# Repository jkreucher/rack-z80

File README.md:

# Rack Z80 Computer

Copyright 2021 Jannik Kreucher

**NOTE: This Project is still work in progress and not working at this point !**

## Table of Contents
 - [About The Project](#about-the-project)
 - [Folder Structure](#folder-structure)
 - [Modules](#modules)

## About The Project

The goal of this project is to understand how computers and operating systems work. This is a collection of hardware and software to create a multi purpose 8-Bit computer with the popular [ZiLog Z80](https://de.wikipedia.org/wiki/Zilog_Z80) processor as the heart of this project. Everything is contained in a [Eurocard Subrack](https://en.wikipedia.org/wiki/Eurocard_(printed_circuit_board)) formfactor because I really like the industrial look to it. This makes it really flexible and easy to expand (and good looking of course). All the parts used should still be manufacured and every PCB is etched at home so everyone can reproduce this project. I know chinese PCB houses are fairly cheap these days but I love tinkering and I have the PCB right away and dont need to wait 2 weeks for the next revision because it seems like the first design is never working.

## Folder Structure

The project is divided into following directories:
 - code
 - schematics
 - tools

[`schematics/`](schematics) contains all the PCBs I designed for this project. Each board has its own README file for way more detailed information. [`code/`](code) contains the source code for the Z80 computer itself. The directory [`tools/`](tools) contains everything needed to compile, assemble source code and other software for this project.

## Modules
To get more information about one module click on the link.
 - [Processor Board](schematics/RackZ80_Processor)
 - [RS232 Serial Interface](schematics/RackZ80_RS232)

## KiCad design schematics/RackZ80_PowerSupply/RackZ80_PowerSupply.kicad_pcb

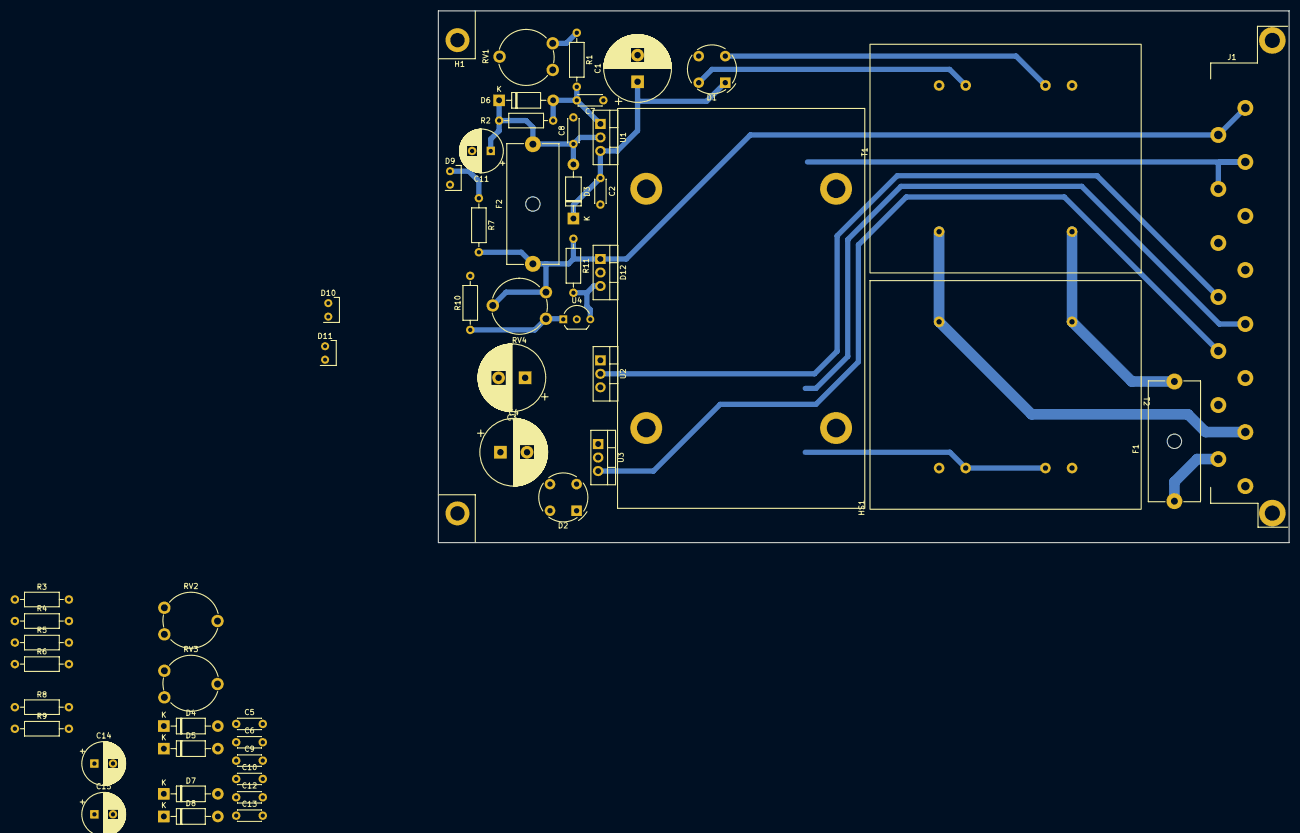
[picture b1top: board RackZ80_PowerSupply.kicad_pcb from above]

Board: 2 copper layers, 160.0 x 100.0 mm, 53 parts (0 on the bottom side), 27 nets.

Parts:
C1, C3, C4: 2200u; CP_Radial_D12.5mm_P5.00mm
C2, C5, C6, C7, C8, C9, C10, C12, C13: 100n; C_Disc_D4.3mm_W1.9mm_P5.00mm
C11, C14, C15: 470u; CP_Radial_D8.0mm_P3.50mm
D1, D2: D_Bridge_+A-A; Diode_Bridge_Round_D9.0mm
D3, D4, D5, D6, D7, D8: 1N4002; D_DO-41_SOD81_P10.16mm_Horizontal
D9, D10, D11: LED; LED_Kingbright_T-1_3mm
D12: BT138; TO-220-3_Vertical
F1: 100mA Slow; Fuseholder_Cylinder-5x20mm_Schurter_0031_8201_Horizontal_Op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
F2: 1A Fast; Fuseholder_Cylinder-5x20mm_Schurter_0031_8201_Horizontal_Op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
H1: FrontPanel; Eurocard_FrontPanel
HS1: Heatsink; Heatsink_Fischer_SK68_75mm
J1: DIN41612 H15; DIN41612_H_right_angle
R1, R8, R9: 1k; R_Axial_DIN0207_L6.3mm_D2.5mm_P10.16mm_Horizontal
R2, R10: 470R; R_Axial_DIN0207_L6.3mm_D2.5mm_P10.16mm_Horizontal
R3, R4: 1k8; R_Axial_DIN0207_L6.3mm_D2.5mm_P10.16mm_Horizontal
R5, R6, R7, R11: 240R; R_Axial_DIN0207_L6.3mm_D2.5mm_P10.16mm_Horizontal
RV1, RV2, RV3, RV4: 1k; Potentiometer_Piher_PT-10-V10_Vertical
T1: Transformer_1P_1S; BlockTrafo_10VA
T2: Transformer_1P_2S; BlockTrafo_10VA
U1, U2: LM317_TO-220; TO-220-3_Vertical
U3: LM337_TO220; TO-220-3_Vertical
U4: TL431; TO-92_Inline_Wide

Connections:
+5V: D12.1 (A1), F2.2, J1.4, J1.6, R7.2, R11.1, RV4.1, RV4.2
+15V: C12.1, C14.1, D4.2 (A), D7.1 (K), J1.18, R5.2, R8.1, U2.2 (VO)
-15V: C13.2, C15.2, D5.1 (K), D8.2 (A), J1.22, R6.1, R9.1, U3.3 (VO)
/L: F1.1, J1.30
/N: J1.28, T1.6 (AB), T2.1 (AA)
GND1: C1.2, C2.2, C7.2, C8.2, C11.2, D1.3 (-), D9.1 (K), D12.2 (A2), J1.8, J1.10, R10.2, RV1.2, RV1.3, U4.2 (A)
GND2: C3.2, C4.1, C5.2, C6.1, C9.2, C10.1, C12.2, C13.1, C14.2, C15.1, D10.1 (K), D11.2 (A), J1.20, RV2.2, RV2.3, RV3.1, RV3.2, T2.8 (SB), T2.11 (SC)
unnamed: C1.1, C2.1, D1.1 (+), D3.1 (K), U1.3 (VI)
unnamed: C3.1, C5.1, D2.1 (+), D4.1 (K), U2.3 (VI)
unnamed: C4.2, C6.2, D2.3 (-), D5.2 (A), U3.2 (VI)
unnamed: C8.1, C11.1, D3.2 (A), D6.1 (K), F2.1, R2.2, U1.2 (VO)
unnamed: C7.1, D6.2 (A), R1.2, R2.1, U1.1 (ADJ)
unnamed: C9.1, D7.2 (A), R3.2, R5.1, U2.1 (ADJ)
unnamed: C10.2, D8.1 (K), R4.1, R6.2, U3.1 (ADJ)
unnamed: D9.2 (A), R7.1
unnamed: D10.2 (A), R8.2
unnamed: D11.1 (K), R9.2
unnamed: D12.3 (G), R11.2, U4.3 (K)
unnamed: R1.1, RV1.1
unnamed: R3.1, RV2.1
unnamed: R4.2, RV3.3
unnamed: F1.2, T1.1 (AA), T2.6 (AB)
unnamed: D1.4, T1.8 (SA)
unnamed: D1.2, T1.11 (SB)
unnamed: D2.4, T2.7 (SA)
unnamed: D2.2, T2.12 (SD)
unnamed: R10.1, RV4.3, U4.1 (REF)

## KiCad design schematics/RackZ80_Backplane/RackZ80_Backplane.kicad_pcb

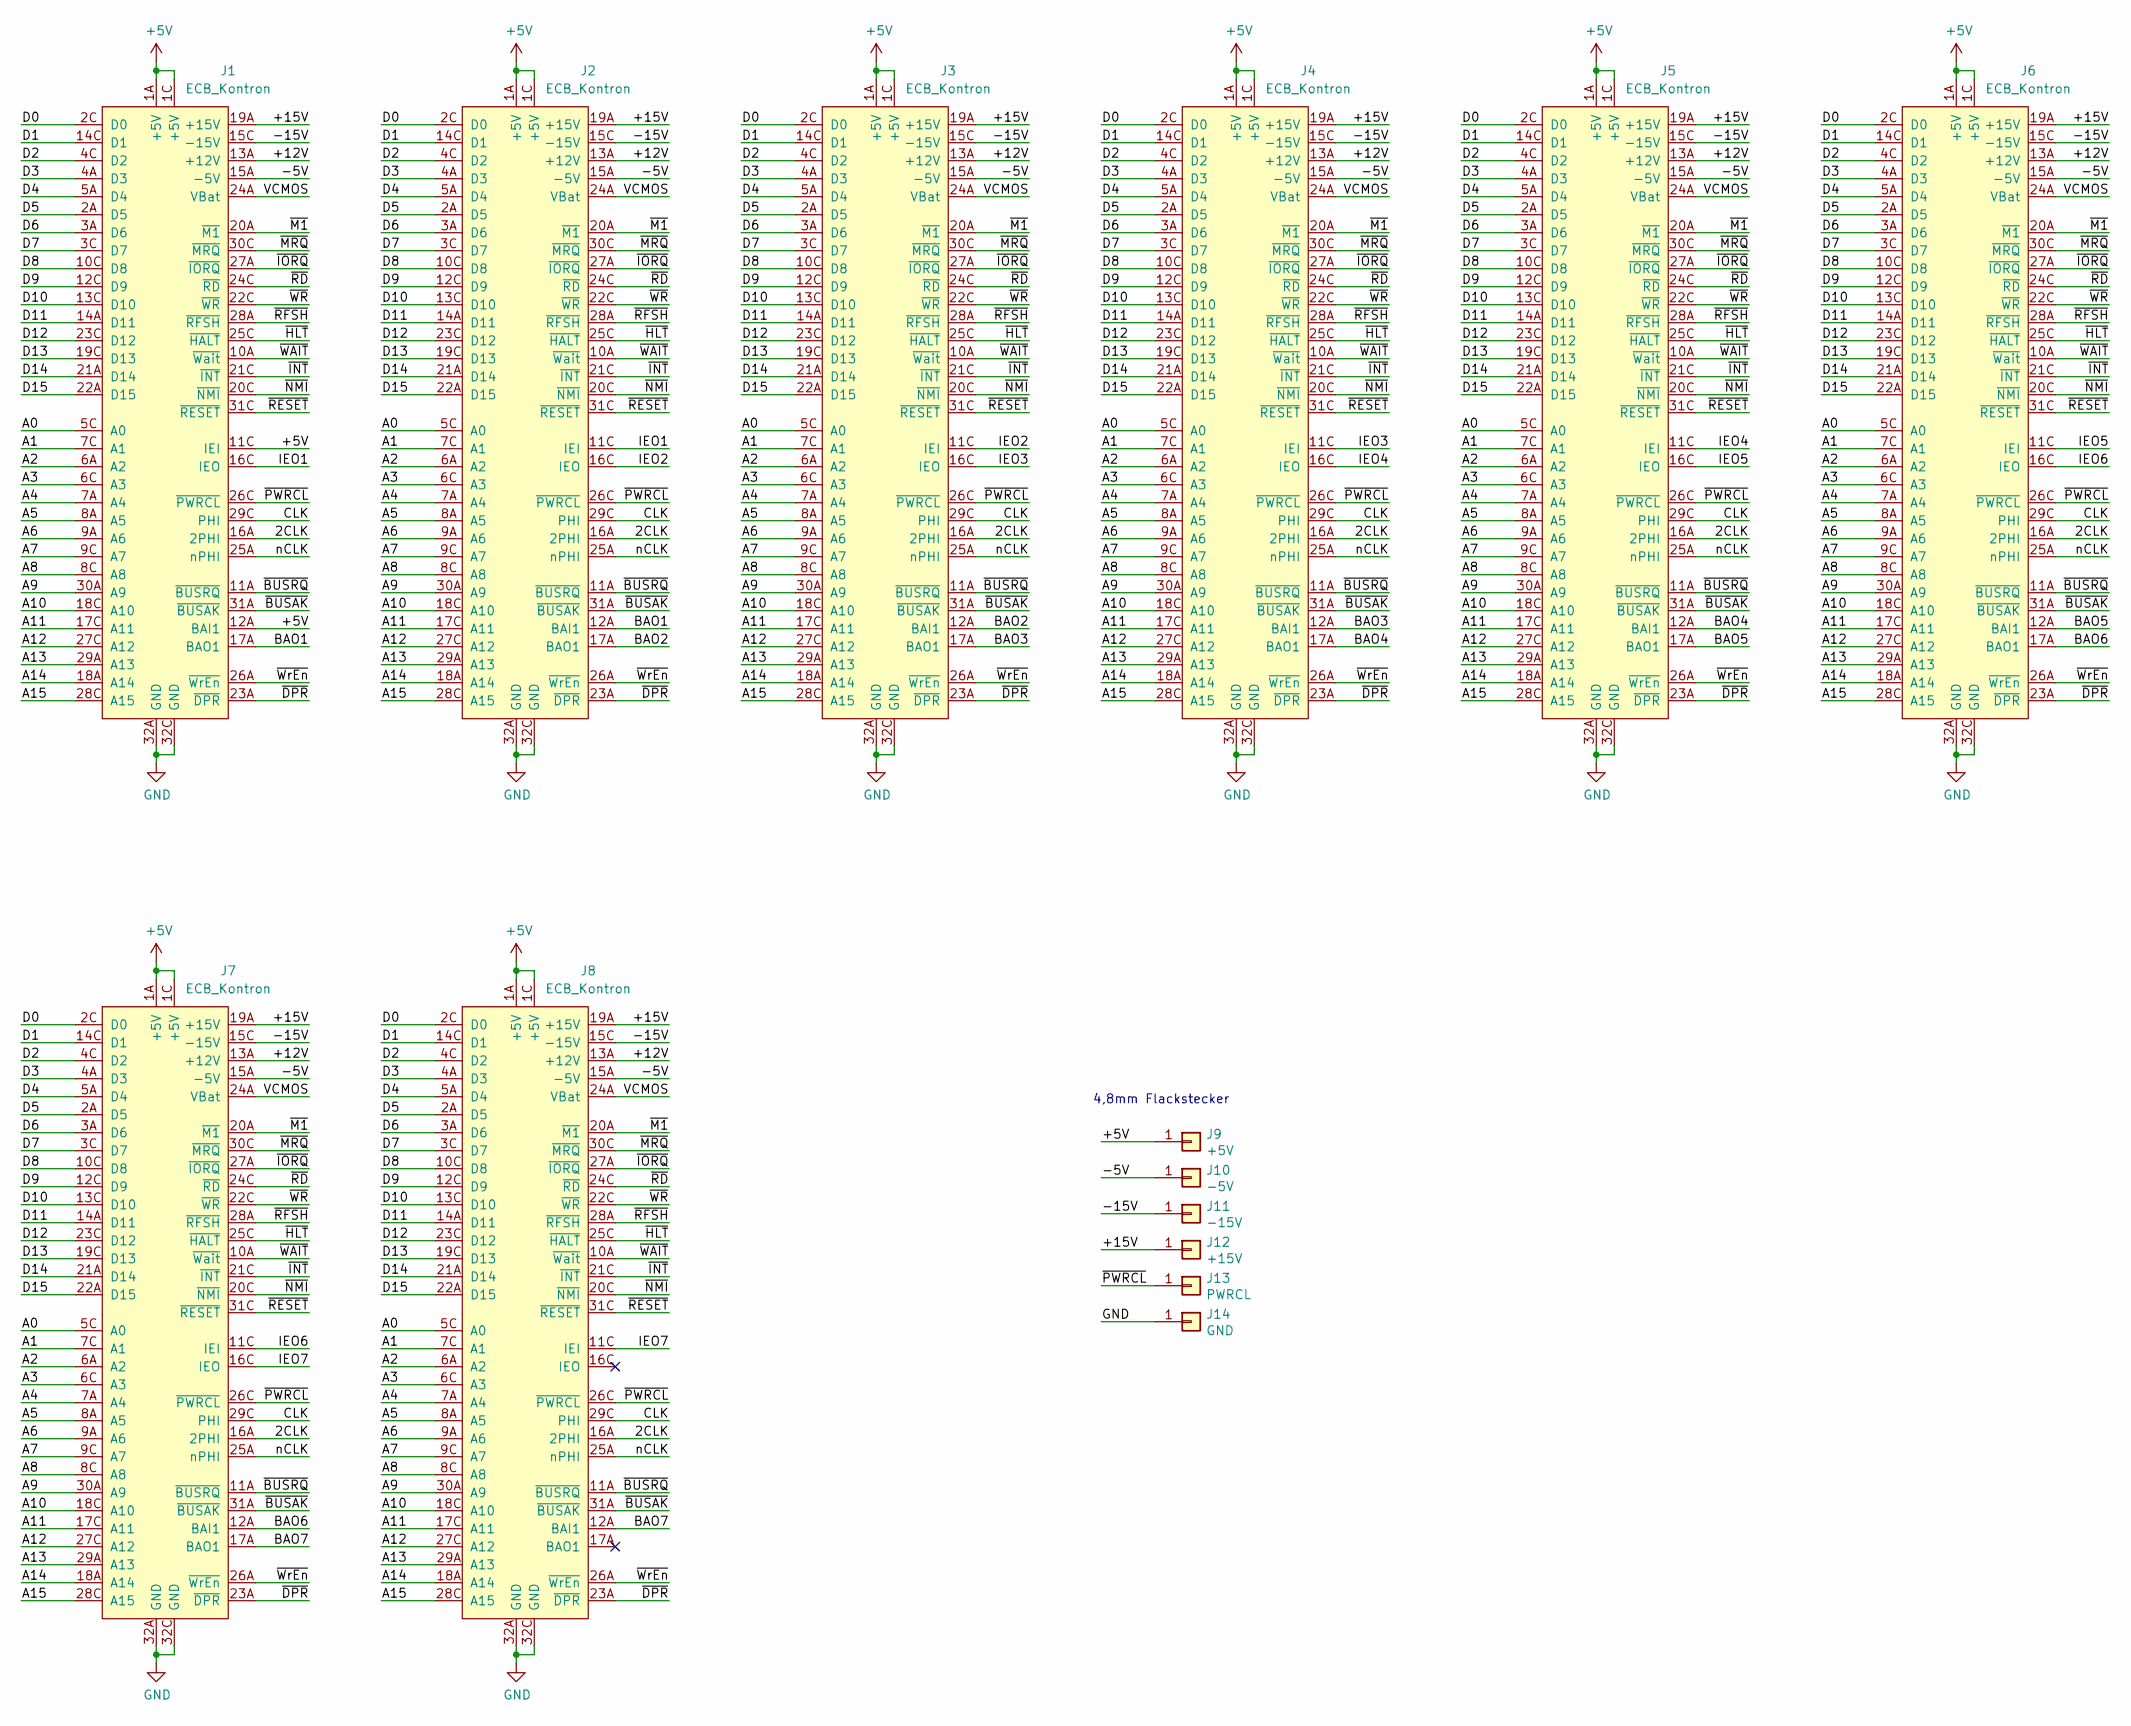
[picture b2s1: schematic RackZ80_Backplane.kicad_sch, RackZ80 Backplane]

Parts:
J1, J2, J3, J4, J5, J6, J7, J8: ECB_Kontron; Eurocard_DIN41612_C64_Female
J9: +5V; Flat_Spade_Connector_5.0mm
J10: -5V; Flat_Spade_Connector_5.0mm
J11: -15V; Flat_Spade_Connector_5.0mm
J12: +15V; Flat_Spade_Connector_5.0mm
J13: PWRCL; Flat_Spade_Connector_5.0mm
J14: GND; Flat_Spade_Connector_5.0mm

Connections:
+5V: J1.1A (+5V), J1.1C (+5V), J1.11C (IEI), J1.12A (BAI1), J2.1A (+5V), J2.1C (+5V), J3.1A (+5V), J3.1C (+5V), J4.1A (+5V), J4.1C (+5V), J5.1A (+5V), J5.1C (+5V), J6.1A (+5V), J6.1C (+5V), J7.1A (+5V), J7.1C (+5V), J8.1A (+5V), J8.1C (+5V), J9.1
/2CLK: J1.16A (2PHI), J2.16A (2PHI), J3.16A (2PHI), J4.16A (2PHI), J5.16A (2PHI), J6.16A (2PHI), J7.16A (2PHI), J8.16A (2PHI)
/+12V: J1.13A (+12V), J2.13A (+12V), J3.13A (+12V), J4.13A (+12V), J5.13A (+12V), J6.13A (+12V), J7.13A (+12V), J8.13A (+12V)
/+15V: J1.19A (+15V), J2.19A (+15V), J3.19A (+15V), J4.19A (+15V), J5.19A (+15V), J6.19A (+15V), J7.19A (+15V), J8.19A (+15V), J12.1
/-5V: J1.15A (-5V), J2.15A (-5V), J3.15A (-5V), J4.15A (-5V), J5.15A (-5V), J6.15A (-5V), J7.15A (-5V), J8.15A (-5V), J10.1
/-15V: J1.15C (-15V), J2.15C (-15V), J3.15C (-15V), J4.15C (-15V), J5.15C (-15V), J6.15C (-15V), J7.15C (-15V), J8.15C (-15V), J11.1
/A0: J1.5C (A0), J2.5C (A0), J3.5C (A0), J4.5C (A0), J5.5C (A0), J6.5C (A0), J7.5C (A0), J8.5C (A0)
/A1: J1.7C (A1), J2.7C (A1), J3.7C (A1), J4.7C (A1), J5.7C (A1), J6.7C (A1), J7.7C (A1), J8.7C (A1)
/A2: J1.6A (A2), J2.6A (A2), J3.6A (A2), J4.6A (A2), J5.6A (A2), J6.6A (A2), J7.6A (A2), J8.6A (A2)
/A3: J1.6C (A3), J2.6C (A3), J3.6C (A3), J4.6C (A3), J5.6C (A3), J6.6C (A3), J7.6C (A3), J8.6C (A3)
/A4: J1.7A (A4), J2.7A (A4), J3.7A (A4), J4.7A (A4), J5.7A (A4), J6.7A (A4), J7.7A (A4), J8.7A (A4)
/A5: J1.8A (A5), J2.8A (A5), J3.8A (A5), J4.8A (A5), J5.8A (A5), J6.8A (A5), J7.8A (A5), J8.8A (A5)
/A6: J1.9A (A6), J2.9A (A6), J3.9A (A6), J4.9A (A6), J5.9A (A6), J6.9A (A6), J7.9A (A6), J8.9A (A6)
/A7: J1.9C (A7), J2.9C (A7), J3.9C (A7), J4.9C (A7), J5.9C (A7), J6.9C (A7), J7.9C (A7), J8.9C (A7)
/A8: J1.8C (A8), J2.8C (A8), J3.8C (A8), J4.8C (A8), J5.8C (A8), J6.8C (A8), J7.8C (A8), J8.8C (A8)
/A9: J1.30A (A9), J2.30A (A9), J3.30A (A9), J4.30A (A9), J5.30A (A9), J6.30A (A9), J7.30A (A9), J8.30A (A9)
/A10: J1.18C (A10), J2.18C (A10), J3.18C (A10), J4.18C (A10), J5.18C (A10), J6.18C (A10), J7.18C (A10), J8.18C (A10)
/A11: J1.17C (A11), J2.17C (A11), J3.17C (A11), J4.17C (A11), J5.17C (A11), J6.17C (A11), J7.17C (A11), J8.17C (A11)
/A12: J1.27C (A12), J2.27C (A12), J3.27C (A12), J4.27C (A12), J5.27C (A12), J6.27C (A12), J7.27C (A12), J8.27C (A12)
/A13: J1.29A (A13), J2.29A (A13), J3.29A (A13), J4.29A (A13), J5.29A (A13), J6.29A (A13), J7.29A (A13), J8.29A (A13)
/A14: J1.18A (A14), J2.18A (A14), J3.18A (A14), J4.18A (A14), J5.18A (A14), J6.18A (A14), J7.18A (A14), J8.18A (A14)
/A15: J1.28C (A15), J2.28C (A15), J3.28C (A15), J4.28C (A15), J5.28C (A15), J6.28C (A15), J7.28C (A15), J8.28C (A15)
/BAO1: J1.17A (BAO1), J2.12A (BAI1)
/BAO2: J2.17A (BAO1), J3.12A (BAI1)
/BAO3: J3.17A (BAO1), J4.12A (BAI1)
/BAO4: J4.17A (BAO1), J5.12A (BAI1)
/BAO5: J5.17A (BAO1), J6.12A (BAI1)
/BAO6: J6.17A (BAO1), J7.12A (BAI1)
/BAO7: J7.17A (BAO1), J8.12A (BAI1)
/CLK: J1.29C (PHI), J2.29C (PHI), J3.29C (PHI), J4.29C (PHI), J5.29C (PHI), J6.29C (PHI), J7.29C (PHI), J8.29C (PHI)
/D0: J1.2C (D0), J2.2C (D0), J3.2C (D0), J4.2C (D0), J5.2C (D0), J6.2C (D0), J7.2C (D0), J8.2C (D0)
/D1: J1.14C (D1), J2.14C (D1), J3.14C (D1), J4.14C (D1), J5.14C (D1), J6.14C (D1), J7.14C (D1), J8.14C (D1)
/D2: J1.4C (D2), J2.4C (D2), J3.4C (D2), J4.4C (D2), J5.4C (D2), J6.4C (D2), J7.4C (D2), J8.4C (D2)
/D3: J1.4A (D3), J2.4A (D3), J3.4A (D3), J4.4A (D3), J5.4A (D3), J6.4A (D3), J7.4A (D3), J8.4A (D3)
/D4: J1.5A (D4), J2.5A (D4), J3.5A (D4), J4.5A (D4), J5.5A (D4), J6.5A (D4), J7.5A (D4), J8.5A (D4)
/D5: J1.2A (D5), J2.2A (D5), J3.2A (D5), J4.2A (D5), J5.2A (D5), J6.2A (D5), J7.2A (D5), J8.2A (D5)
/D6: J1.3A (D6), J2.3A (D6), J3.3A (D6), J4.3A (D6), J5.3A (D6), J6.3A (D6), J7.3A (D6), J8.3A (D6)
/D7: J1.3C (D7), J2.3C (D7), J3.3C (D7), J4.3C (D7), J5.3C (D7), J6.3C (D7), J7.3C (D7), J8.3C (D7)
/D8: J1.10C (D8), J2.10C (D8), J3.10C (D8), J4.10C (D8), J5.10C (D8), J6.10C (D8), J7.10C (D8), J8.10C (D8)
/D9: J1.12C (D9), J2.12C (D9), J3.12C (D9), J4.12C (D9), J5.12C (D9), J6.12C (D9), J7.12C (D9), J8.12C (D9)
/D10: J1.13C (D10), J2.13C (D10), J3.13C (D10), J4.13C (D10), J5.13C (D10), J6.13C (D10), J7.13C (D10), J8.13C (D10)
/D11: J1.14A (D11), J2.14A (D11), J3.14A (D11), J4.14A (D11), J5.14A (D11), J6.14A (D11), J7.14A (D11), J8.14A (D11)
/D12: J1.23C (D12), J2.23C (D12), J3.23C (D12), J4.23C (D12), J5.23C (D12), J6.23C (D12), J7.23C (D12), J8.23C (D12)
/D13: J1.19C (D13), J2.19C (D13), J3.19C (D13), J4.19C (D13), J5.19C (D13), J6.19C (D13), J7.19C (D13), J8.19C (D13)
/D14: J1.21A (D14), J2.21A (D14), J3.21A (D14), J4.21A (D14), J5.21A (D14), J6.21A (D14), J7.21A (D14), J8.21A (D14)
/D15: J1.22A (D15), J2.22A (D15), J3.22A (D15), J4.22A (D15), J5.22A (D15), J6.22A (D15), J7.22A (D15), J8.22A (D15)
/IEO1: J1.16C (IEO), J2.11C (IEI)
/IEO2: J2.16C (IEO), J3.11C (IEI)
/IEO3: J3.16C (IEO), J4.11C (IEI)
/IEO4: J4.16C (IEO), J5.11C (IEI)
/IEO5: J5.16C (IEO), J6.11C (IEI)
/IEO6: J6.16C (IEO), J7.11C (IEI)
/IEO7: J7.16C (IEO), J8.11C (IEI)
/VCMOS: J1.24A (VBat), J2.24A (VBat), J3.24A (VBat), J4.24A (VBat), J5.24A (VBat), J6.24A (VBat), J7.24A (VBat), J8.24A (VBat)
/nCLK: J1.25A (nPHI), J2.25A (nPHI), J3.25A (nPHI), J4.25A (nPHI), J5.25A (nPHI), J6.25A (nPHI), J7.25A (nPHI), J8.25A (nPHI)
/~BUSAK: J1.31A (~BUSAK), J2.31A (~BUSAK), J3.31A (~BUSAK), J4.31A (~BUSAK), J5.31A (~BUSAK), J6.31A (~BUSAK), J7.31A (~BUSAK), J8.31A (~BUSAK)
/~BUSRQ: J1.11A (~BUSRQ), J2.11A (~BUSRQ), J3.11A (~BUSRQ), J4.11A (~BUSRQ), J5.11A (~BUSRQ), J6.11A (~BUSRQ), J7.11A (~BUSRQ), J8.11A (~BUSRQ)
/~DPR: J1.23A (~DPR), J2.23A (~DPR), J3.23A (~DPR), J4.23A (~DPR), J5.23A (~DPR), J6.23A (~DPR), J7.23A (~DPR), J8.23A (~DPR)
/~HLT: J1.25C (~HALT), J2.25C (~HALT), J3.25C (~HALT), J4.25C (~HALT), J5.25C (~HALT), J6.25C (~HALT), J7.25C (~HALT), J8.25C (~HALT)
/~INT: J1.21C (~INT), J2.21C (~INT), J3.21C (~INT), J4.21C (~INT), J5.21C (~INT), J6.21C (~INT), J7.21C (~INT), J8.21C (~INT)
/~IORQ: J1.27A (~IORQ), J2.27A (~IORQ), J3.27A (~IORQ), J4.27A (~IORQ), J5.27A (~IORQ), J6.27A (~IORQ), J7.27A (~IORQ), J8.27A (~IORQ)
/~M1: J1.20A (~M1), J2.20A (~M1), J3.20A (~M1), J4.20A (~M1), J5.20A (~M1), J6.20A (~M1), J7.20A (~M1), J8.20A (~M1)
/~MRQ: J1.30C (~MRQ), J2.30C (~MRQ), J3.30C (~MRQ), J4.30C (~MRQ), J5.30C (~MRQ), J6.30C (~MRQ), J7.30C (~MRQ), J8.30C (~MRQ)
/~NMI: J1.20C (~NMI), J2.20C (~NMI), J3.20C (~NMI), J4.20C (~NMI), J5.20C (~NMI), J6.20C (~NMI), J7.20C (~NMI), J8.20C (~NMI)
/~PWRCL: J1.26C (~PWRCL), J2.26C (~PWRCL), J3.26C (~PWRCL), J4.26C (~PWRCL), J5.26C (~PWRCL), J6.26C (~PWRCL), J7.26C (~PWRCL), J8.26C (~PWRCL), J13.1
/~RD: J1.24C (~RD), J2.24C (~RD), J3.24C (~RD), J4.24C (~RD), J5.24C (~RD), J6.24C (~RD), J7.24C (~RD), J8.24C (~RD)
/~RESET: J1.31C (~RESET), J2.31C (~RESET), J3.31C (~RESET), J4.31C (~RESET), J5.31C (~RESET), J6.31C (~RESET), J7.31C (~RESET), J8.31C (~RESET)
/~RFSH: J1.28A (~RFSH), J2.28A (~RFSH), J3.28A (~RFSH), J4.28A (~RFSH), J5.28A (~RFSH), J6.28A (~RFSH), J7.28A (~RFSH), J8.28A (~RFSH)
/~WAIT: J1.10A (~Wait), J2.10A (~Wait), J3.10A (~Wait), J4.10A (~Wait), J5.10A (~Wait), J6.10A (~Wait), J7.10A (~Wait), J8.10A (~Wait)
/~WR: J1.22C (~WR), J2.22C (~WR), J3.22C (~WR), J4.22C (~WR), J5.22C (~WR), J6.22C (~WR), J7.22C (~WR), J8.22C (~WR)
/~WrEn: J1.26A (~WrEn), J2.26A (~WrEn), J3.26A (~WrEn), J4.26A (~WrEn), J5.26A (~WrEn), J6.26A (~WrEn), J7.26A (~WrEn), J8.26A (~WrEn)
GND: J1.32A (GND), J1.32C (GND), J2.32A (GND), J2.32C (GND), J3.32A (GND), J3.32C (GND), J4.32A (GND), J4.32C (GND), J5.32A (GND), J5.32C (GND), J6.32A (GND), J6.32C (GND), J7.32A (GND), J7.32C (GND), J8.32A (GND), J8.32C (GND), J14.1

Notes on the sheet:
4,8mm Flackstecker

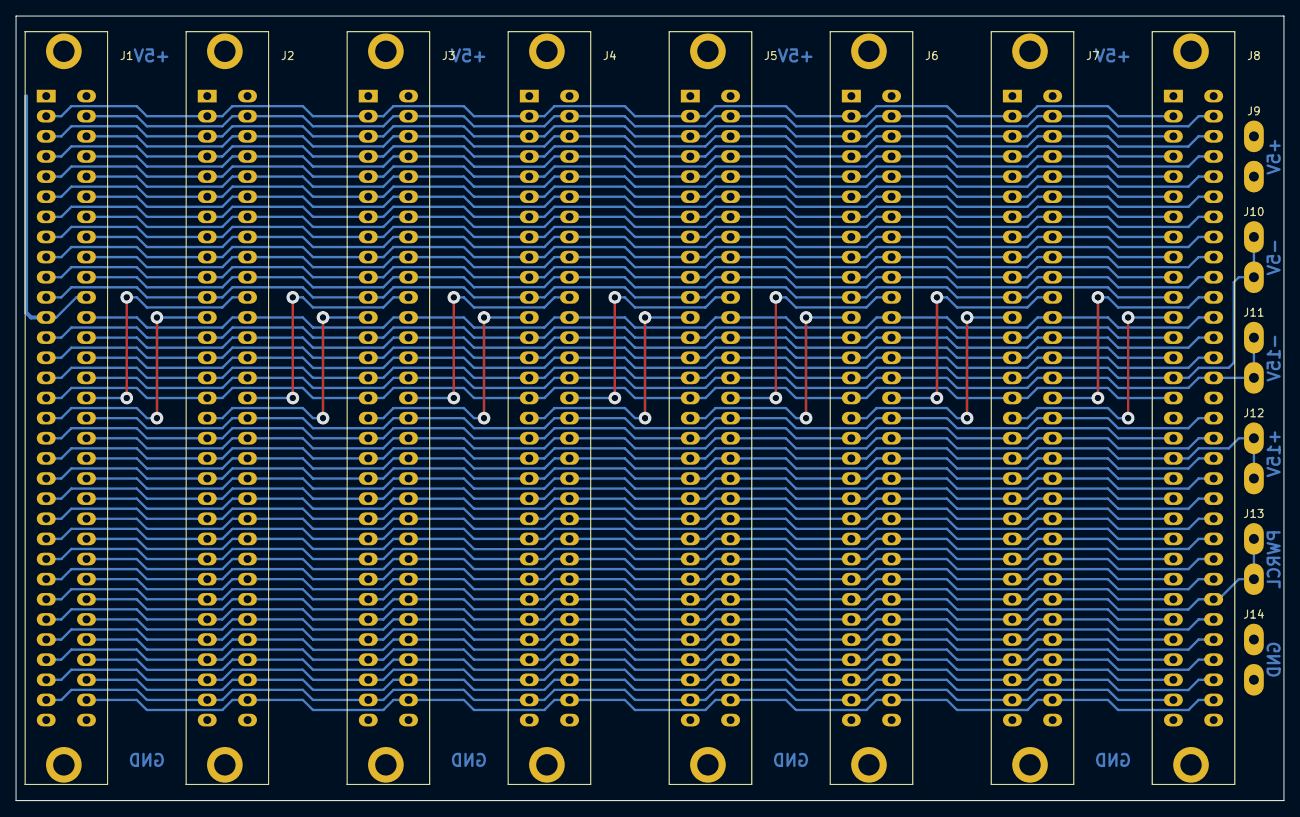
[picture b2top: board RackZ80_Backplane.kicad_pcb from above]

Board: 2 copper layers, 160.0 x 99.0 mm, 14 parts (0 on the bottom side), 72 nets.

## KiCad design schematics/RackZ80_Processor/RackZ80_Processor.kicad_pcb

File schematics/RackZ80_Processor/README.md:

# Processor Board

Copyright 2021 Jannik Kreucher

## Table of Contents
 - [How it works](#how-it-works)
 - [Schematic](#schematic)

## How it works
TODO

## Schematic
The [schematic](documentation/RackZ80_Processor.pdf) exported as pdf. So it is ready to print.

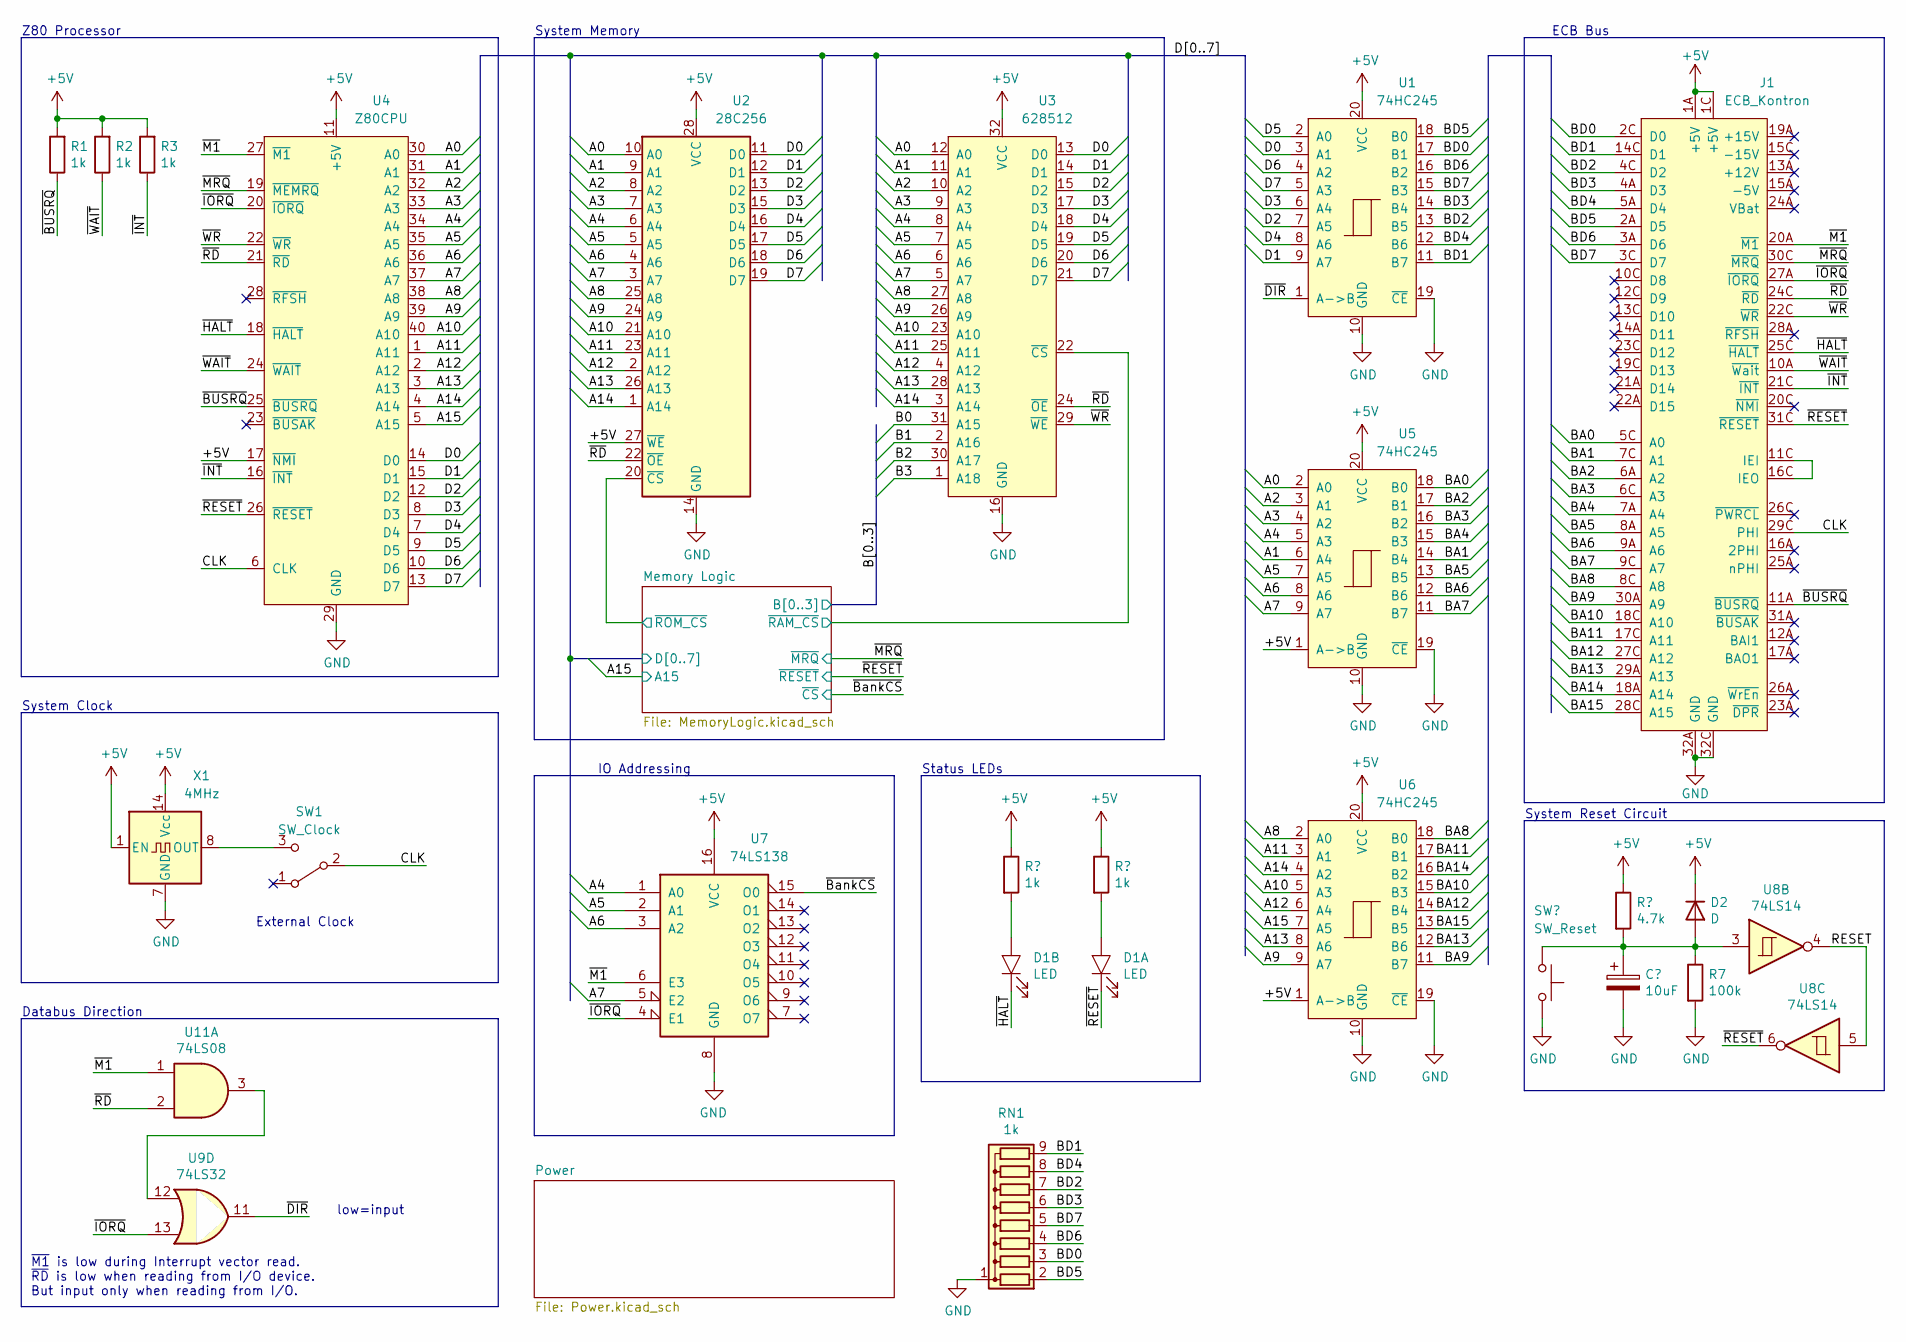
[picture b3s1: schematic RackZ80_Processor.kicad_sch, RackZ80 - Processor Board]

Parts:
C1: 10uF; CP_Radial_D5.0mm_P2.50mm
D1: LED; LED_Array_2
D2: D; D_DO-35_SOD27_P10.16mm_Horizontal
J1: ECB_Kontron; Eurocard_DIN41612_C64_Male
R1, R2, R3, R4, R5: 1k; R_Axial_DIN0207_L6.3mm_D2.5mm_P10.16mm_Horizontal
R6: 4.7k; R_Axial_DIN0207_L6.3mm_D2.5mm_P10.16mm_Horizontal
R7: 100k; R_Axial_DIN0207_L6.3mm_D2.5mm_P10.16mm_Horizontal
RN1: 1k; R_Array_SIP9
SW1: SW_Clock; SW_MS-500
SW2: SW_Reset; SW_MS-500
U1, U5, U6: 74HC245; DIP-20_Socket
U2: 28C256; DIP-28_Socket_Wide
U3: 628512; DIP-32_Socket_Wide
U4: Z80CPU; DIP-40_Socket_Wide
U7: 74LS138; DIP-16_Socket
U8: 74LS14; DIP-14_Socket
U9: 74LS32
U11: 74LS08; DIP-14_Socket
X1: 4MHz; DIP-14_Oscillator_Socket

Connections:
+5V: D2.1 (K), J1.1A (+5V), J1.1C (+5V), R1.2, R2.2, R3.2, R4.1, R5.1, R6.1, U1.20 (VCC), U2.27 (~WE), U2.28 (VCC), U3.32 (VCC), U4.11 (+5V), U4.17 (~NMI), U5.1 (A->B), U5.20 (VCC), U6.1 (A->B), U6.20 (VCC), U7.16 (VCC), X1.1 (EN), X1.14 (Vcc); also elsewhere on the board
/A0: U2.10 (A0), U3.12 (A0), U4.30 (A0), U5.2 (A0)
/A1: U2.9 (A1), U3.11 (A1), U4.31 (A1), U5.6 (A4)
/A2: U2.8 (A2), U3.10 (A2), U4.32 (A2), U5.3 (A1)
/A3: U2.7 (A3), U3.9 (A3), U4.33 (A3), U5.4 (A2)
/A4: U2.6 (A4), U3.8 (A4), U4.34 (A4), U5.5 (A3), U7.1 (A0)
/A5: U2.5 (A5), U3.7 (A5), U4.35 (A5), U5.7 (A5), U7.2 (A1)
/A6: U2.4 (A6), U3.6 (A6), U4.36 (A6), U5.8 (A6), U7.3 (A2)
/A7: U2.3 (A7), U3.5 (A7), U4.37 (A7), U5.9 (A7), U7.5 (E2)
/A8: U2.25 (A8), U3.27 (A8), U4.38 (A8), U6.2 (A0)
/A9: U2.24 (A9), U3.26 (A9), U4.39 (A9), U6.9 (A7)
/A10: U2.21 (A10), U3.23 (A10), U4.40 (A10), U6.5 (A3)
/A11: U2.23 (A11), U3.25 (A11), U4.1 (A11), U6.3 (A1)
/A12: U2.2 (A12), U3.4 (A12), U4.2 (A12), U6.6 (A4)
/A13: U2.26 (A13), U3.28 (A13), U4.3 (A13), U6.8 (A6)
/A14: U2.1 (A14), U3.3 (A14), U4.4 (A14), U6.4 (A2)
/A15: U4.5 (A15), U6.7 (A5); also elsewhere on the board
/B0: U3.31 (A15); also elsewhere on the board
/B1: U3.2 (A16); also elsewhere on the board
/B2: U3.30 (A17); also elsewhere on the board
/B3: U3.1 (A18); also elsewhere on the board
/BA0: J1.5C (A0), U5.18 (B0)
/BA1: J1.7C (A1), U5.14 (B4)
/BA2: J1.6A (A2), U5.17 (B1)
/BA3: J1.6C (A3), U5.16 (B2)
/BA4: J1.7A (A4), U5.15 (B3)
/BA5: J1.8A (A5), U5.13 (B5)
/BA6: J1.9A (A6), U5.12 (B6)
/BA7: J1.9C (A7), U5.11 (B7)
/BA8: J1.8C (A8), U6.18 (B0)
/BA9: J1.30A (A9), U6.11 (B7)
/BA10: J1.18C (A10), U6.15 (B3)
/BA11: J1.17C (A11), U6.17 (B1)
/BA12: J1.27C (A12), U6.14 (B4)
/BA13: J1.29A (A13), U6.12 (B6)
/BA14: J1.18A (A14), U6.16 (B2)
/BA15: J1.28C (A15), U6.13 (B5)
/BD0: J1.2C (D0), RN1.3 (R2), U1.17 (B1)
/BD1: J1.14C (D1), RN1.9 (R8), U1.11 (B7)
/BD2: J1.4C (D2), RN1.7 (R6), U1.13 (B5)
/BD3: J1.4A (D3), RN1.6 (R5), U1.14 (B4)
/BD4: J1.5A (D4), RN1.8 (R7), U1.12 (B6)
/BD5: J1.2A (D5), RN1.2 (R1), U1.18 (B0)
/BD6: J1.3A (D6), RN1.4 (R3), U1.16 (B2)
/BD7: J1.3C (D7), RN1.5 (R4), U1.15 (B3)
/CLK: J1.29C (PHI), SW1.2 (B), U4.6 (CLK)
/D0: U1.3 (A1), U2.11 (D0), U3.13 (D0), U4.14 (D0); also elsewhere on the board
/D1: U1.9 (A7), U2.12 (D1), U3.14 (D1), U4.15 (D1); also elsewhere on the board
/D2: U1.7 (A5), U2.13 (D2), U3.15 (D2), U4.12 (D2); also elsewhere on the board
/D3: U1.6 (A4), U2.15 (D3), U3.17 (D3), U4.8 (D3); also elsewhere on the board
/D4: U1.8 (A6), U2.16 (D4), U3.18 (D4), U4.7 (D4); also elsewhere on the board
/D5: U1.2 (A0), U2.17 (D5), U3.19 (D5), U4.9 (D5)
/D6: U1.4 (A2), U2.18 (D6), U3.20 (D6), U4.10 (D6)
/D7: U1.5 (A3), U2.19 (D7), U3.21 (D7), U4.13 (D7)
/Memory Logic/~RAM_CS: U3.22 (~CS); also elsewhere on the board
/Memory Logic/~ROM_CS: U2.20 (~CS); also elsewhere on the board
/RESET: U8.4, U8.5
/~BUSRQ: J1.11A (~BUSRQ), R1.1, U4.25 (~BUSRQ)
/~BankCS: U7.15 (O0); also elsewhere on the board
/~DIR: U1.1 (A->B), U9.11
/~HALT: D1.3 (K), J1.25C (~HALT), U4.18 (~HALT)
/~INT: J1.21C (~INT), R3.1, U4.16 (~INT)
/~IORQ: J1.27A (~IORQ), U4.20 (~IORQ), U7.4 (E1), U9.13
/~M1: J1.20A (~M1), U4.27 (~M1), U7.6 (E3), U11.1
/~MRQ: J1.30C (~MRQ), U4.19 (~MEMRQ); also elsewhere on the board
/~RD: J1.24C (~RD), U2.22 (~OE), U3.24 (~OE), U4.21 (~RD), U11.2
/~RESET: D1.1 (K), J1.31C (~RESET), U4.26 (~RESET), U8.6; also elsewhere on the board
/~WAIT: J1.10A (~Wait), R2.1, U4.24 (~WAIT)
/~WR: J1.22C (~WR), U3.29 (~WE), U4.22 (~WR)
GND: C1.2, J1.32A (GND), J1.32C (GND), R7.2, RN1.1 (common), SW2.1, U1.10 (GND), U1.19 (~CE), U2.14 (GND), U3.16 (GND), U4.29 (GND), U5.10 (GND), U5.19 (~CE), U6.10 (GND), U6.19 (~CE), U7.8 (GND), X1.7 (GND); also elsewhere on the board
unnamed: C1.1, D2.2 (A), R6.2, R7.1, SW2.2, U8.3
unnamed: D1.2 (A), R5.2
unnamed: D1.4 (A), R4.2
unnamed: J1.11C (IEI), J1.16C (IEO)
unnamed: SW1.3 (C), X1.8 (OUT)
unnamed: U9.12, U11.3

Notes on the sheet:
System Reset Circuit
Databus Direction
low=input
IO Addressing
Status LEDs
Z80 Processor
~{M1} is low during Interrupt vector read. ~{RD} is low when reading from I/O device. But input only when reading from I/O.
External Clock
System Memory
System Clock
ECB Bus

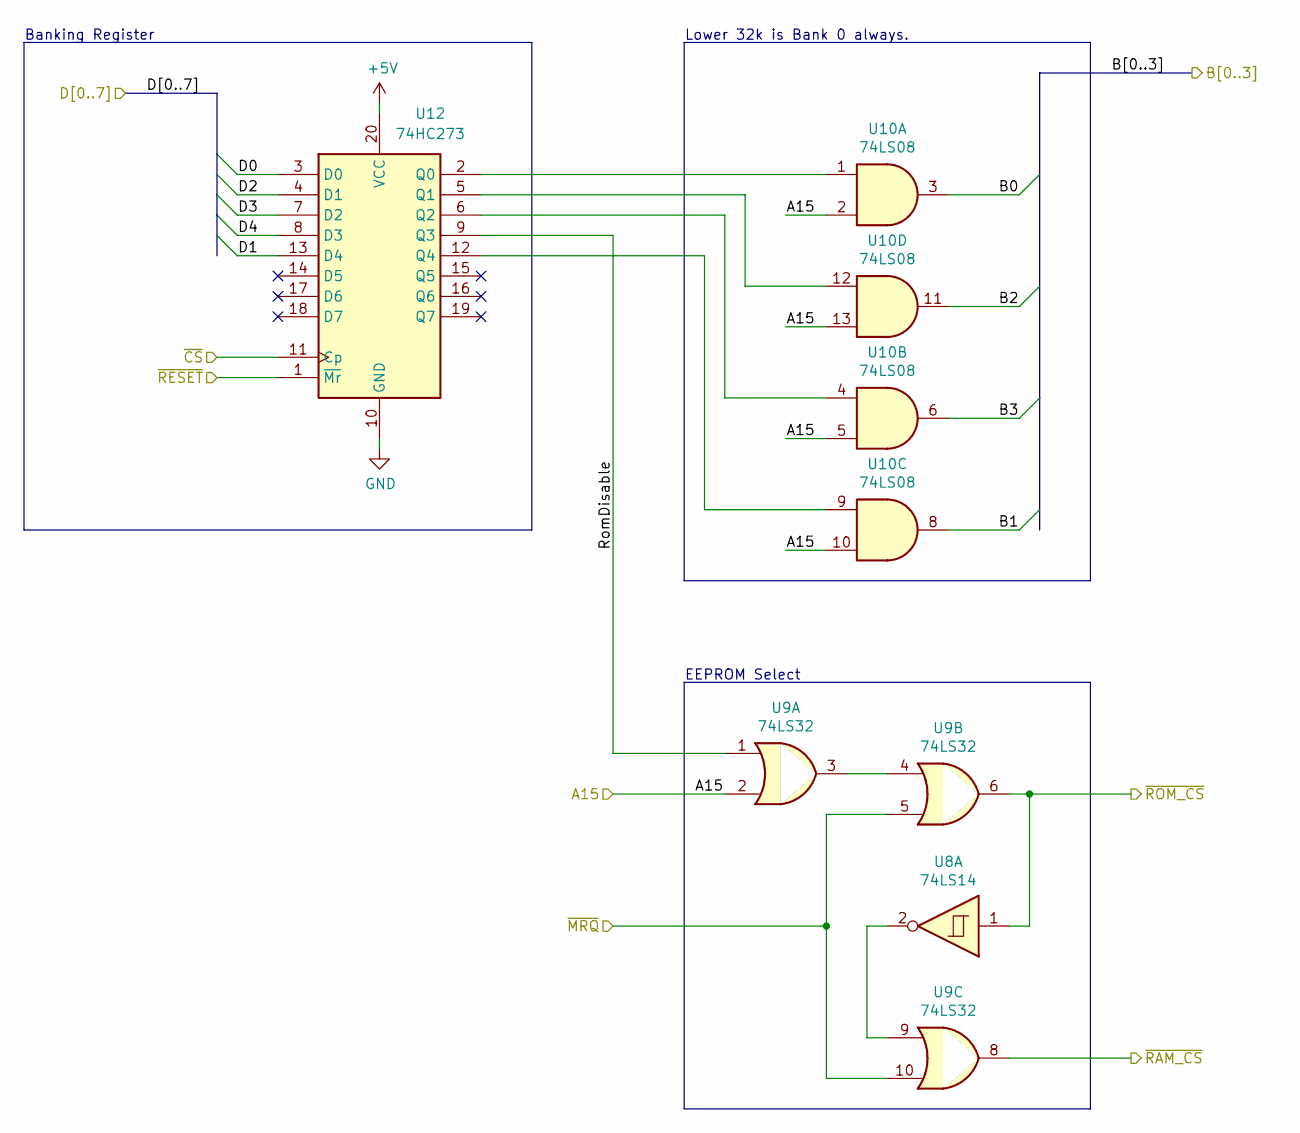
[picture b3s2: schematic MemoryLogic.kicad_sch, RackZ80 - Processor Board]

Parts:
U8: 74LS14; DIP-14_Socket
U9: 74LS32; DIP-14_Socket
U10: 74LS08; DIP-14_Socket
U12: 74HC273; DIP-20_Socket

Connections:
+5V: U12.20 (VCC); also elsewhere on the board
/A15: U9.2, U10.2, U10.5, U10.10, U10.13; also elsewhere on the board
/B0: U10.3; also elsewhere on the board
/B1: U10.8; also elsewhere on the board
/B2: U10.11; also elsewhere on the board
/B3: U10.6; also elsewhere on the board
/D0: U12.3 (D0); also elsewhere on the board
/D1: U12.13 (D4); also elsewhere on the board
/D2: U12.4 (D1); also elsewhere on the board
/D3: U12.7 (D2); also elsewhere on the board
/D4: U12.8 (D3); also elsewhere on the board
/Memory Logic/RomDisable: U9.1, U12.9 (Q3)
/Memory Logic/~RAM_CS: U9.8; also elsewhere on the board
/Memory Logic/~ROM_CS: U8.1, U9.6; also elsewhere on the board
/~BankCS: U12.11 (Cp); also elsewhere on the board
/~MRQ: U9.5, U9.10; also elsewhere on the board
/~RESET: U12.1 (~Mr); also elsewhere on the board
GND: U12.10 (GND); also elsewhere on the board
unnamed: U8.2, U9.9
unnamed: U9.3, U9.4
unnamed: U10.1, U12.2 (Q0)
unnamed: U10.4, U12.6 (Q2)
unnamed: U10.9, U12.12 (Q4)
unnamed: U10.12, U12.5 (Q1)

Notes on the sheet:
Banking Register
Lower 32k is Bank 0 always.
EEPROM Select

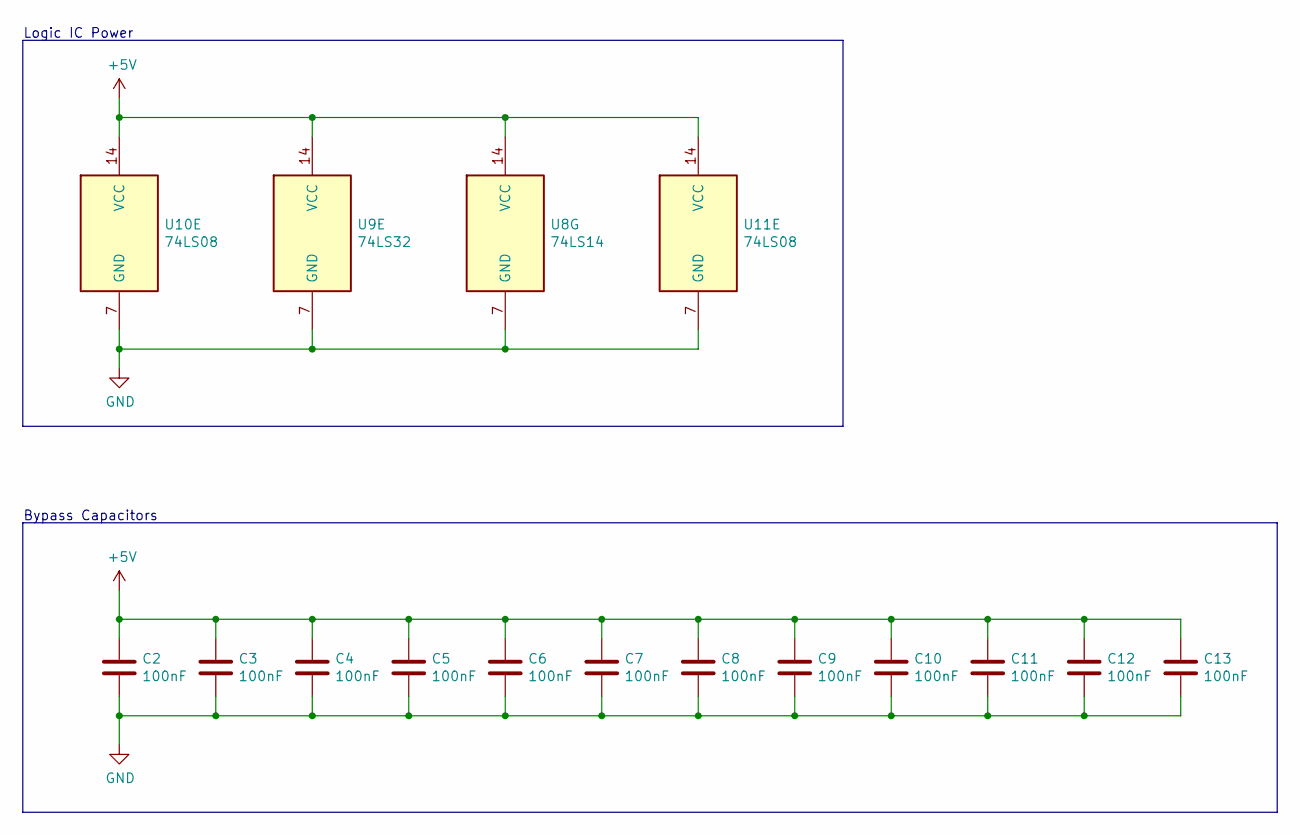
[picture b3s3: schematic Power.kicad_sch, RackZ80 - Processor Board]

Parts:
C2, C3, C4, C5, C6, C7, C8, C9, C10, C11, C12, C13: 100nF; C_Disc_D4.3mm_W1.9mm_P5.00mm
U8: 74LS14; DIP-14_Socket
U9: 74LS32; DIP-14_Socket
U10, U11: 74LS08; DIP-14_Socket

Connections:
+5V: C2.1, C3.1, C4.1, C5.1, C6.1, C7.1, C8.1, C9.1, C10.1, C11.1, C12.1, C13.1, U8.14 (VCC), U9.14 (VCC), U10.14 (VCC), U11.14 (VCC); also elsewhere on the board
GND: C2.2, C3.2, C4.2, C5.2, C6.2, C7.2, C8.2, C9.2, C10.2, C11.2, C12.2, C13.2, U8.7 (GND), U9.7 (GND), U10.7 (GND), U11.7 (GND); also elsewhere on the board

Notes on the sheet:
Bypass Capacitors
Logic IC Power
